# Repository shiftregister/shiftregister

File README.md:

# shiftregister

Software and hardware for the Shift Register project:  http://shiftregister.info/

Muon detection hardware is based on the work of Robert Hart: http://www.hardhack.org.au/projects

Core memory hardware is based on the work of Wayne Holder: https://sites.google.com/site/wayneholder/one-bit-ferrite-core-memory

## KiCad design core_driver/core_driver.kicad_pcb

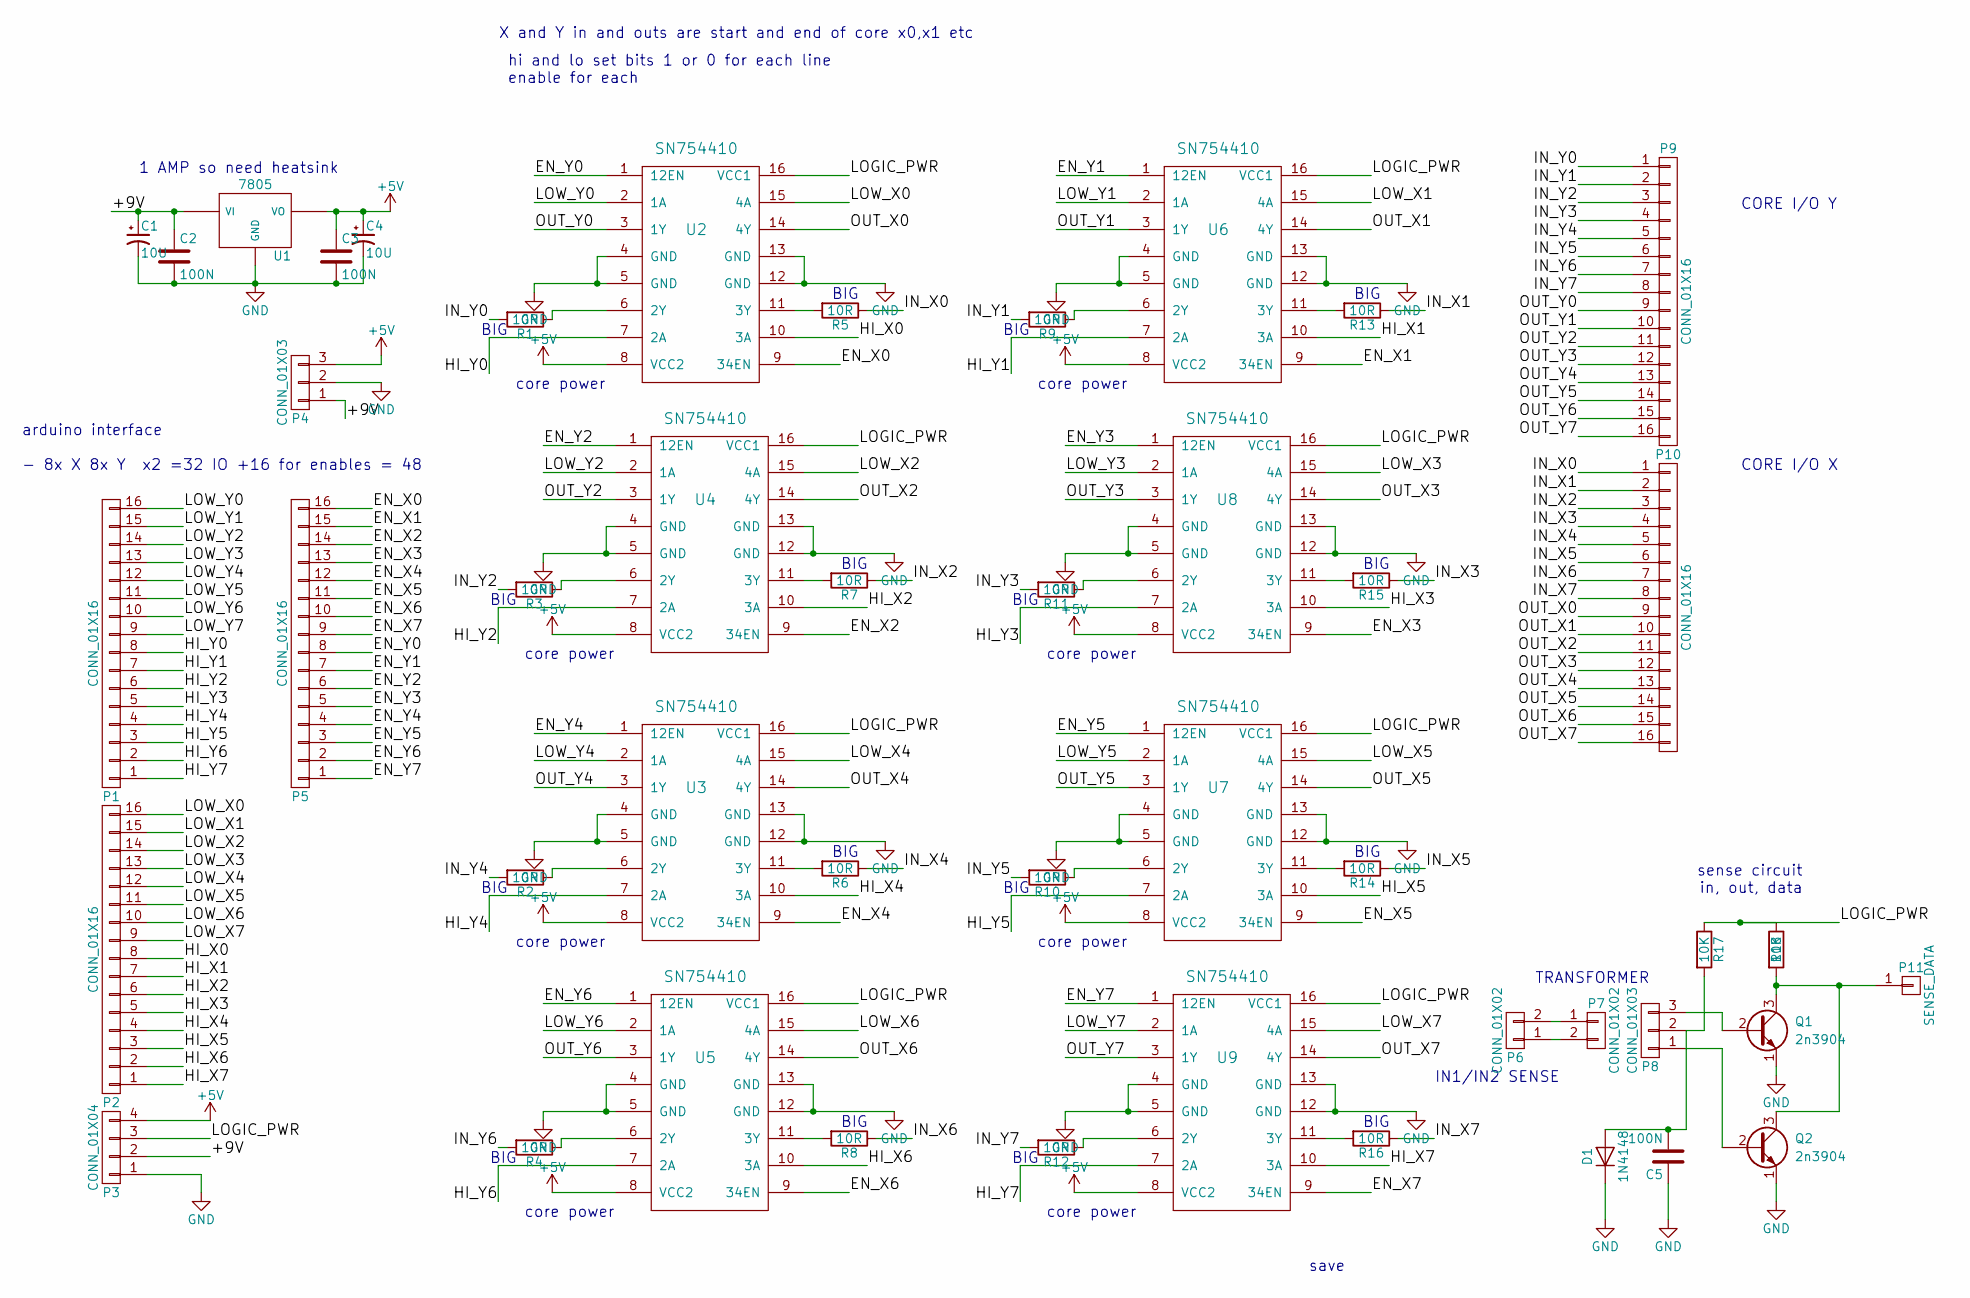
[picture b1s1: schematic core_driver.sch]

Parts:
C1, C4: 10U; CP_Radial_D10.0mm_P5.00mm
C2, C3, C5: 100N; C_Disc_D6.0mm_W2.5mm_P5.00mm
D1: 1N4148; D_DO-35_SOD27_P7.62mm_Horizontal
P1, P2, P5, P9, P10: CONN_01X16; Pin_Header_Straight_1x16_Pitch2.54mm
P3: CONN_01X04; Pin_Header_Straight_1x04_Pitch2.54mm
P4, P8: CONN_01X03; Pin_Header_Straight_1x03_Pitch2.54mm
P6, P7: CONN_01X02; Pin_Header_Straight_1x02_Pitch2.54mm
P11: SENSE_DATA; Pin_Header_Straight_1x01_Pitch2.54mm
Q1, Q2: 2n3904; TO-92_Molded_Wide
R1, R2, R3, R4, R5, R6, R7, R8, R9, R10, R11, R12, R13, R14, R15, R16: 10R; R_Axial_DIN0414_L11.9mm_D4.5mm_P15.24mm_Horizontal
R17, R18: 10K; R_Axial_DIN0204_L3.6mm_D1.6mm_P5.08mm_Horizontal
U1: 7805; TO-220_Vertical
U2, U3, U4, U5, U6, U7, U8, U9: SN754410; DIP-16_W7.62mm_LongPads

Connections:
+5V: C3.1, C4.1, P3.4, P4.3, U1.3, U1.VO, U2.8 (VCC2), U3.8 (VCC2), U4.8 (VCC2), U5.8 (VCC2), U6.8 (VCC2), U7.8 (VCC2), U8.8 (VCC2), U9.8 (VCC2)
/+9V: C1.1, C2.1, P3.2, P4.1, U1.1, U1.VI
/EN_X0: P5.16, U2.9 (34EN)
/EN_X1: P5.15, U6.9 (34EN)
/EN_X2: P5.14, U4.9 (34EN)
/EN_X3: P5.13, U8.9 (34EN)
/EN_X4: P5.12, U3.9 (34EN)
/EN_X5: P5.11, U7.9 (34EN)
/EN_X6: P5.10, U5.9 (34EN)
/EN_X7: P5.9, U9.9 (34EN)
/EN_Y0: P5.8, U2.1 (12EN)
/EN_Y1: P5.7, U6.1 (12EN)
/EN_Y2: P5.6, U4.1 (12EN)
/EN_Y3: P5.5, U8.1 (12EN)
/EN_Y4: P5.4, U3.1 (12EN)
/EN_Y5: P5.3, U7.1 (12EN)
/EN_Y6: P5.2, U5.1 (12EN)
/EN_Y7: P5.1, U9.1 (12EN)
/HI_X0: P2.8, U2.10 (3A)
/HI_X1: P2.7, U6.10 (3A)
/HI_X2: P2.6, U4.10 (3A)
/HI_X3: P2.5, U8.10 (3A)
/HI_X4: P2.4, U3.10 (3A)
/HI_X5: P2.3, U7.10 (3A)
/HI_X6: P2.2, U5.10 (3A)
/HI_X7: P2.1, U9.10 (3A)
/HI_Y0: P1.8, U2.7 (2A)
/HI_Y1: P1.7, U6.7 (2A)
/HI_Y2: P1.6, U4.7 (2A)
/HI_Y3: P1.5, U8.7 (2A)
/HI_Y4: P1.4, U3.7 (2A)
/HI_Y5: P1.3, U7.7 (2A)
/HI_Y6: P1.2, U5.7 (2A)
/HI_Y7: P1.1, U9.7 (2A)
/IN_X0: P10.1, R5.1
/IN_X1: P10.2, R13.1
/IN_X2: P10.3, R7.1
/IN_X3: P10.4, R15.1
/IN_X4: P10.5, R6.1
/IN_X5: P10.6, R14.1
/IN_X6: P10.7, R8.1
/IN_X7: P10.8, R16.1
/IN_Y0: P9.1, R1.2
/IN_Y1: P9.2, R9.2
/IN_Y2: P9.3, R3.2
/IN_Y3: P9.4, R11.2
/IN_Y4: P9.5, R2.2
/IN_Y5: P9.6, R10.2
/IN_Y6: P9.7, R4.2
/IN_Y7: P9.8, R12.2
/LOGIC_PWR: P3.3, R17.1, R18.1, U2.16 (VCC1), U3.16 (VCC1), U4.16 (VCC1), U5.16 (VCC1), U6.16 (VCC1), U7.16 (VCC1), U8.16 (VCC1), U9.16 (VCC1)
/LOW_X0: P2.16, U2.15 (4A)
/LOW_X1: P2.15, U6.15 (4A)
/LOW_X2: P2.14, U4.15 (4A)
/LOW_X3: P2.13, U8.15 (4A)
/LOW_X4: P2.12, U3.15 (4A)
/LOW_X5: P2.11, U7.15 (4A)
/LOW_X6: P2.10, U5.15 (4A)
/LOW_X7: P2.9, U9.15 (4A)
/LOW_Y0: P1.16, U2.2 (1A)
/LOW_Y1: P1.15, U6.2 (1A)
/LOW_Y2: P1.14, U4.2 (1A)
/LOW_Y3: P1.13, U8.2 (1A)
/LOW_Y4: P1.12, U3.2 (1A)
/LOW_Y5: P1.11, U7.2 (1A)
/LOW_Y6: P1.10, U5.2 (1A)
/LOW_Y7: P1.9, U9.2 (1A)
/OUT_X0: P10.9, U2.14 (4Y)
/OUT_X1: P10.10, U6.14 (4Y)
/OUT_X2: P10.11, U4.14 (4Y)
/OUT_X3: P10.12, U8.14 (4Y)
/OUT_X4: P10.13, U3.14 (4Y)
/OUT_X5: P10.14, U7.14 (4Y)
/OUT_X6: P10.15, U5.14 (4Y)
/OUT_X7: P10.16, U9.14 (4Y)
/OUT_Y0: P9.9, U2.3 (1Y)
/OUT_Y1: P9.10, U6.3 (1Y)
/OUT_Y2: P9.11, U4.3 (1Y)
/OUT_Y3: P9.12, U8.3 (1Y)
/OUT_Y4: P9.13, U3.3 (1Y)
/OUT_Y5: P9.14, U7.3 (1Y)
/OUT_Y6: P9.15, U5.3 (1Y)
/OUT_Y7: P9.16, U9.3 (1Y)
GND: C1.2, C2.2, C3.2, C4.2, C5.1, D1.1 (K), P3.1, P4.2, Q1.1 (E), Q2.1 (E), U1.2, U1.GND, U2.4 (GND), U2.5 (GND), U2.12 (GND), U2.13 (GND), U3.4 (GND), U3.5 (GND), U3.12 (GND), U3.13 (GND), U4.4 (GND), U4.5 (GND), U4.12 (GND), U4.13 (GND), U5.4 (GND), U5.5 (GND), U5.12 (GND), U5.13 (GND), U6.4 (GND), U6.5 (GND), U6.12 (GND), U6.13 (GND), U7.4 (GND), U7.5 (GND), U7.12 (GND), U7.13 (GND), U8.4 (GND), U8.5 (GND), U8.12 (GND), U8.13 (GND), U9.4 (GND), U9.5 (GND), U9.12 (GND), U9.13 (GND)
unnamed: C5.2, D1.2 (A), P8.2, R17.2
unnamed: P6.1, P7.2
unnamed: P6.2, P7.1
unnamed: P8.1, Q2.2 (B)
unnamed: P8.3, Q1.2 (B)
unnamed: P11.1, Q1.3 (C), Q2.3 (C), R18.2
unnamed: R1.1, U2.6 (2Y)
unnamed: R2.1, U3.6 (2Y)
unnamed: R3.1, U4.6 (2Y)
unnamed: R4.1, U5.6 (2Y)
unnamed: R5.2, U2.11 (3Y)
unnamed: R6.2, U3.11 (3Y)
unnamed: R7.2, U4.11 (3Y)
unnamed: R8.2, U5.11 (3Y)
unnamed: R9.1, U6.6 (2Y)
unnamed: R10.1, U7.6 (2Y)
unnamed: R11.1, U8.6 (2Y)
unnamed: R12.1, U9.6 (2Y)
unnamed: R13.2, U6.11 (3Y)
unnamed: R14.2, U7.11 (3Y)
unnamed: R15.2, U8.11 (3Y)
unnamed: R16.2, U9.11 (3Y)

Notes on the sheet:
1 AMP so need heatsink
BIG
CORE I/O X
CORE I/O Y
arduino interface - 8x X 8x Y x2 =32 IO +16 for enables = 48
X and Y in and outs are start and end of core x0,x1 etc
hi and lo set bits 1 or 0 for each line enable for each
sense circuit in, out, data
core power
TRANSFORMER
IN1/IN2 SENSE
save

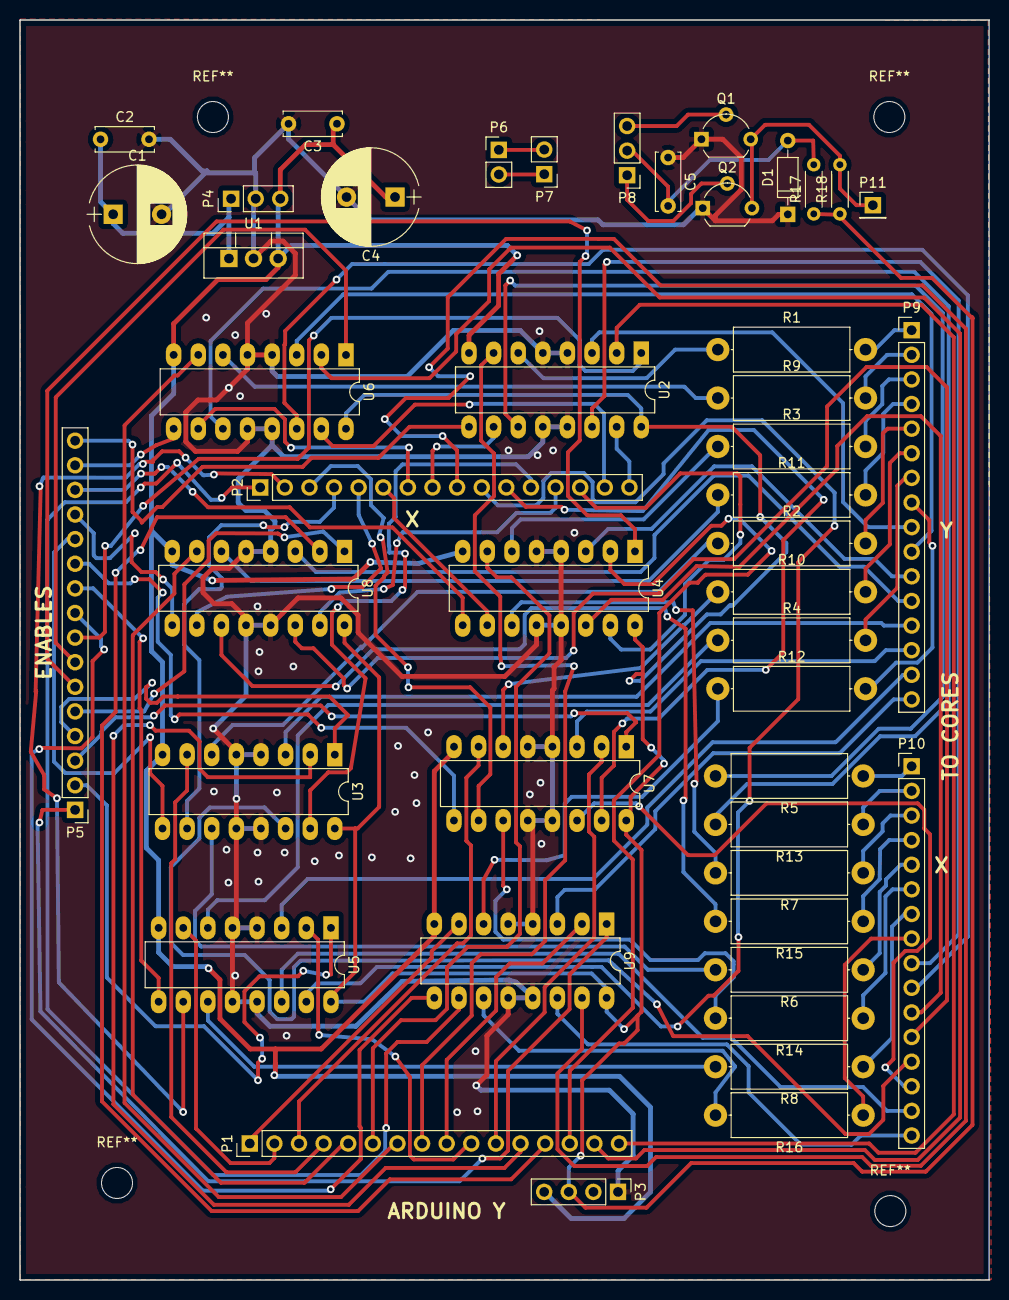
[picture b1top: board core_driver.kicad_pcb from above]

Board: 2 copper layers, 100.0 x 130.0 mm, 46 parts (0 on the bottom side), 106 nets.

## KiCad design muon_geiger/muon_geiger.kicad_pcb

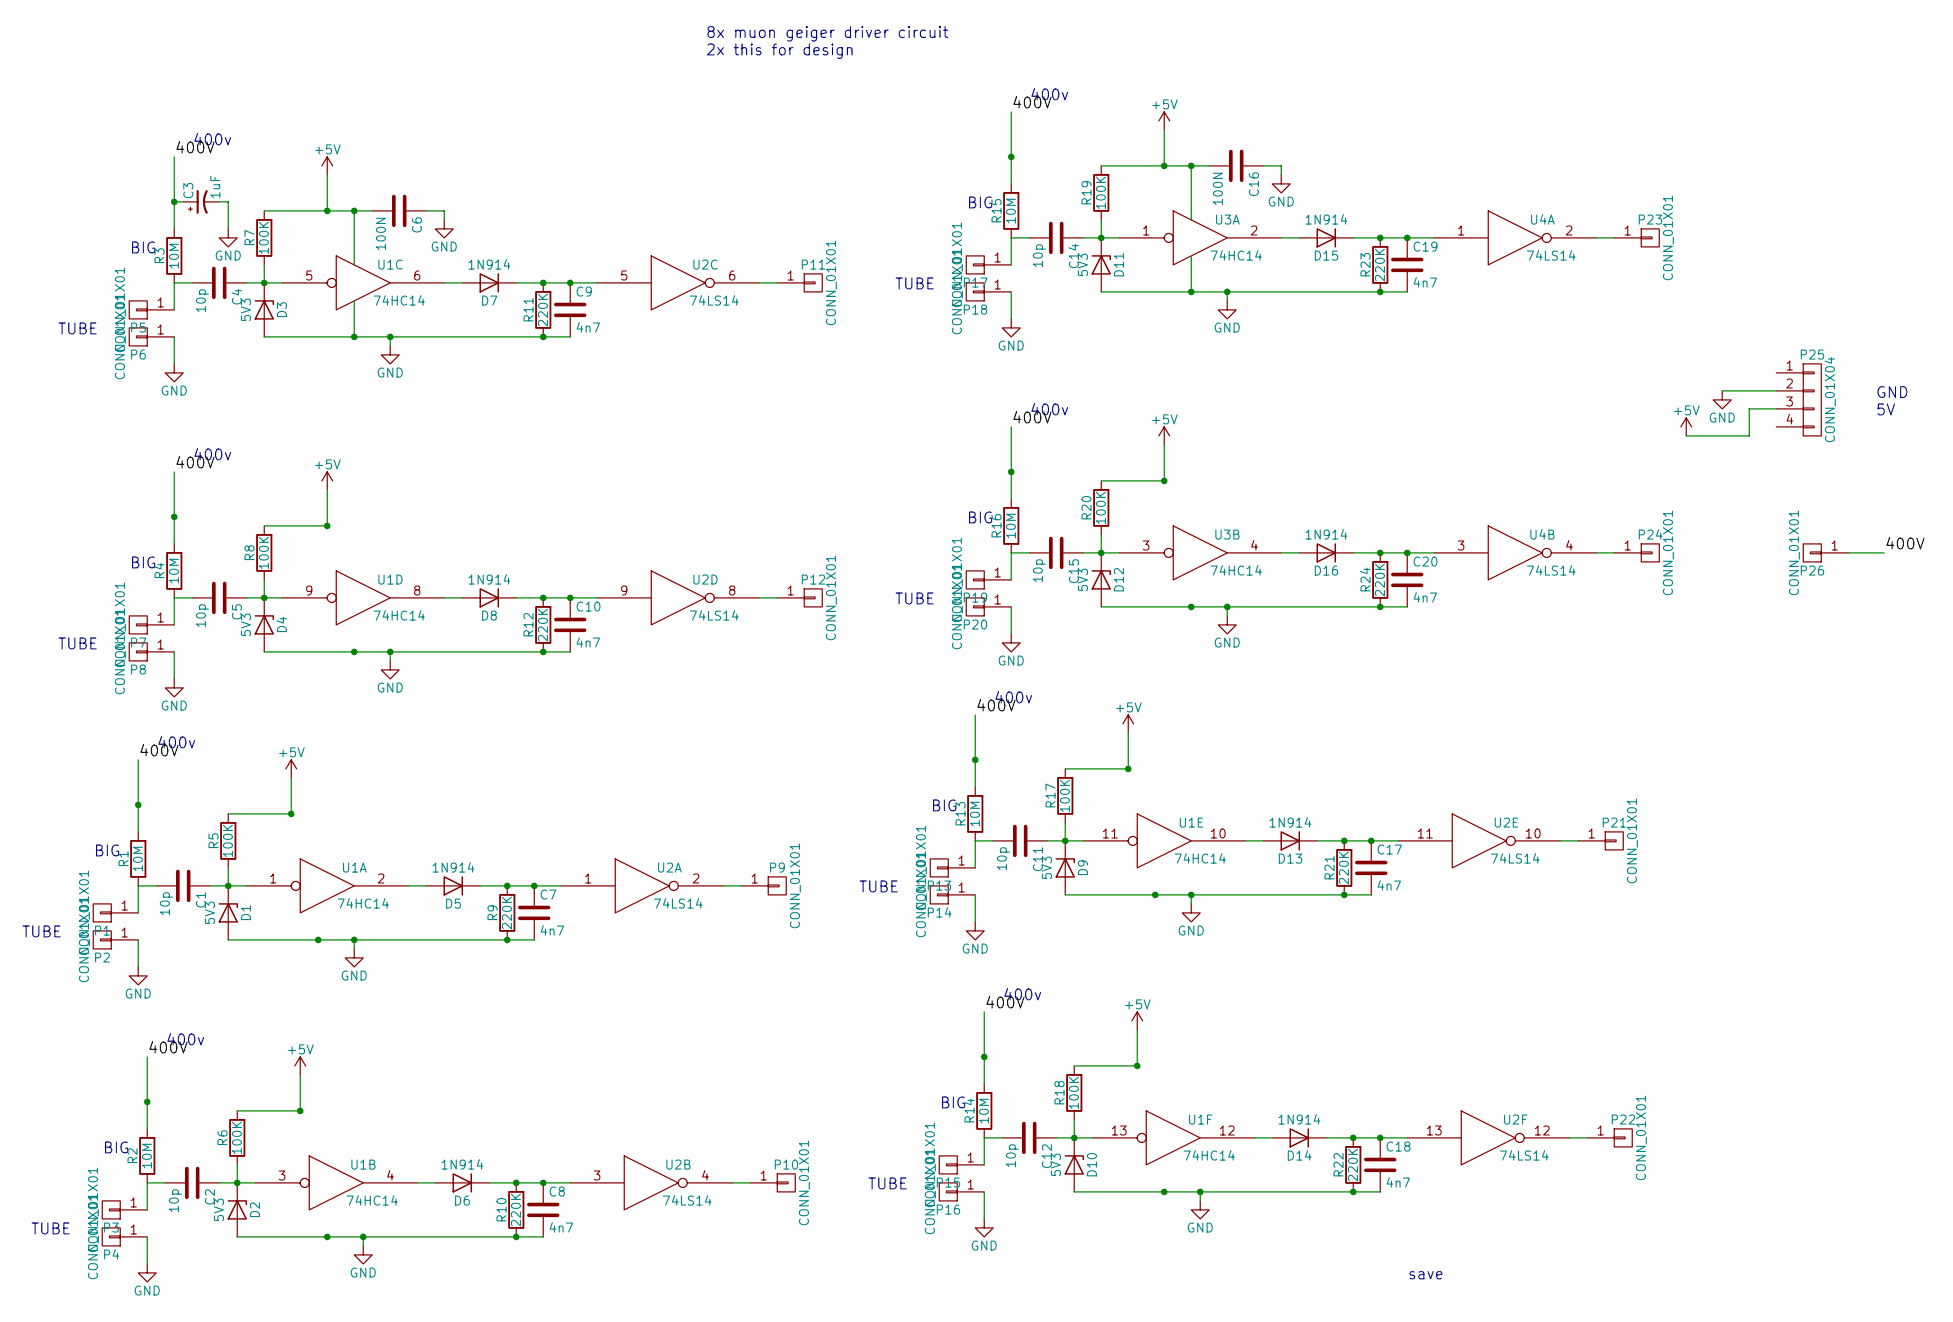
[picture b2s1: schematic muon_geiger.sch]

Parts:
C1, C2, C4, C5, C11, C12, C14, C15: 10p; C_Disc_D6.0mm_W4.4mm_P5.00mm
C3: 1uF; CP_Radial_D10.0mm_P5.00mm
C6, C16: 100N; C_Disc_D3.0mm_W1.6mm_P2.50mm
C7, C8, C9, C10, C17, C18, C19, C20: 4n7; C_Disc_D3.0mm_W1.6mm_P2.50mm
D1, D2, D3, D4, D9, D10, D11, D12: 5V3; D_DO-15_P10.16mm_Horizontal
D5, D6, D7, D8: 1N914; D_DO-35_SOD27_P7.62mm_Horizontal
D13, D14, D15, D16: 1N914; D_DO-15_P10.16mm_Horizontal
P1, P2, P3, P4, P5, P6, P7, P8, P9, P10, P11, P12, P13, P14, P15, P16, P17, P18, P19, P20, P21, P22, P23, P24, P26: CONN_01X01; Pin_Header_Straight_1x01_Pitch2.54mm
P25: CONN_01X04; Pin_Header_Straight_1x04_Pitch2.54mm
R1, R2, R3, R4, R13, R14, R15: 10M; R_Axial_DIN0414_L11.9mm_D4.5mm_P15.24mm_Horizontal
R5, R6, R7, R8, R17, R18, R19, R20: 100K; R_Axial_DIN0207_L6.3mm_D2.5mm_P10.16mm_Horizontal
R9, R10, R11, R12, R21, R22, R23, R24: 220K; R_Axial_DIN0207_L6.3mm_D2.5mm_P10.16mm_Horizontal
R16: 10M; R_Axial_DIN0207_L6.3mm_D2.5mm_P10.16mm_Horizontal
U1, U3: 74HC14; DIP-14_W7.62mm_LongPads
U2, U4: 74LS14; DIP-14_W7.62mm_LongPads

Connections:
+5V: C6.2, C16.2, P25.3, R5.2, R6.2, R7.2, R8.2, R17.2, R18.2, R19.2, R20.2, U1.14 (VCC), U2.14 (VCC), U3.14 (VCC), U4.14 (VCC); also elsewhere on the board
/400V: C3.1, P26.1, R1.2, R2.2, R3.2, R4.2, R13.2, R14.2, R15.2, R16.2
GND: C3.2, C6.1, C7.2, C8.2, C9.2, C10.2, C16.1, C17.2, C18.2, C19.2, C20.2, D1.2 (A), D2.2 (A), D3.2 (A), D4.2 (A), D9.2 (A), D10.2 (A), D11.2 (A), D12.2 (A), P2.1, P4.1, P6.1, P8.1, P14.1, P16.1, P18.1, P20.1, P25.2, R9.1, R10.1, R11.1, R12.1, R21.1, R22.1, R23.1, R24.1, U1.7 (GND), U2.7 (GND), U3.7 (GND), U4.7 (GND); also elsewhere on the board
unnamed: C1.1, D1.1 (K), R5.1, U1.1
unnamed: C1.2, P1.1, R1.1
unnamed: C2.1, D2.1 (K), R6.1, U1.3
unnamed: C2.2, P3.1, R2.1
unnamed: C4.1, D3.1 (K), R7.1, U1.5
unnamed: C4.2, P5.1, R3.1
unnamed: C5.1, D4.1 (K), R8.1, U1.9
unnamed: C5.2, P7.1, R4.1
unnamed: C7.1, D5.1 (K), R9.2, U2.1
unnamed: C8.1, D6.1 (K), R10.2, U2.3
unnamed: C9.1, D7.1 (K), R11.2, U2.5
unnamed: C10.1, D8.1 (K), R12.2, U2.9
unnamed: C11.1, D9.1 (K), R17.1, U1.11
unnamed: C11.2, P13.1, R13.1
unnamed: C12.1, D10.1 (K), R18.1, U1.13
unnamed: C12.2, P15.1, R14.1
unnamed: C14.1, D11.1 (K), R19.1, U3.1
unnamed: C14.2, P17.1, R15.1
unnamed: C15.1, D12.1 (K), R20.1, U3.3
unnamed: C15.2, P19.1, R16.1
unnamed: C17.1, D13.1 (K), R21.2, U2.11
unnamed: C18.1, D14.1 (K), R22.2, U2.13
unnamed: C19.1, D15.1 (K), R23.2, U4.1
unnamed: C20.1, D16.1 (K), R24.2, U4.3
unnamed: D5.2 (A), U1.2
unnamed: D6.2 (A), U1.4
unnamed: D7.2 (A), U1.6
unnamed: D8.2 (A), U1.8
unnamed: D13.2 (A), U1.10
unnamed: D14.2 (A), U1.12
unnamed: D15.2 (A), U3.2
unnamed: D16.2 (A), U3.4
unnamed: P9.1, U2.2
unnamed: P10.1, U2.4
unnamed: P11.1, U2.6
unnamed: P12.1, U2.8
unnamed: P21.1, U2.10
unnamed: P22.1, U2.12
unnamed: P23.1, U4.2
unnamed: P24.1, U4.4

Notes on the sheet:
8x muon geiger driver circuit 2x this for design
400v
TUBE
BIG
GND 5V
save

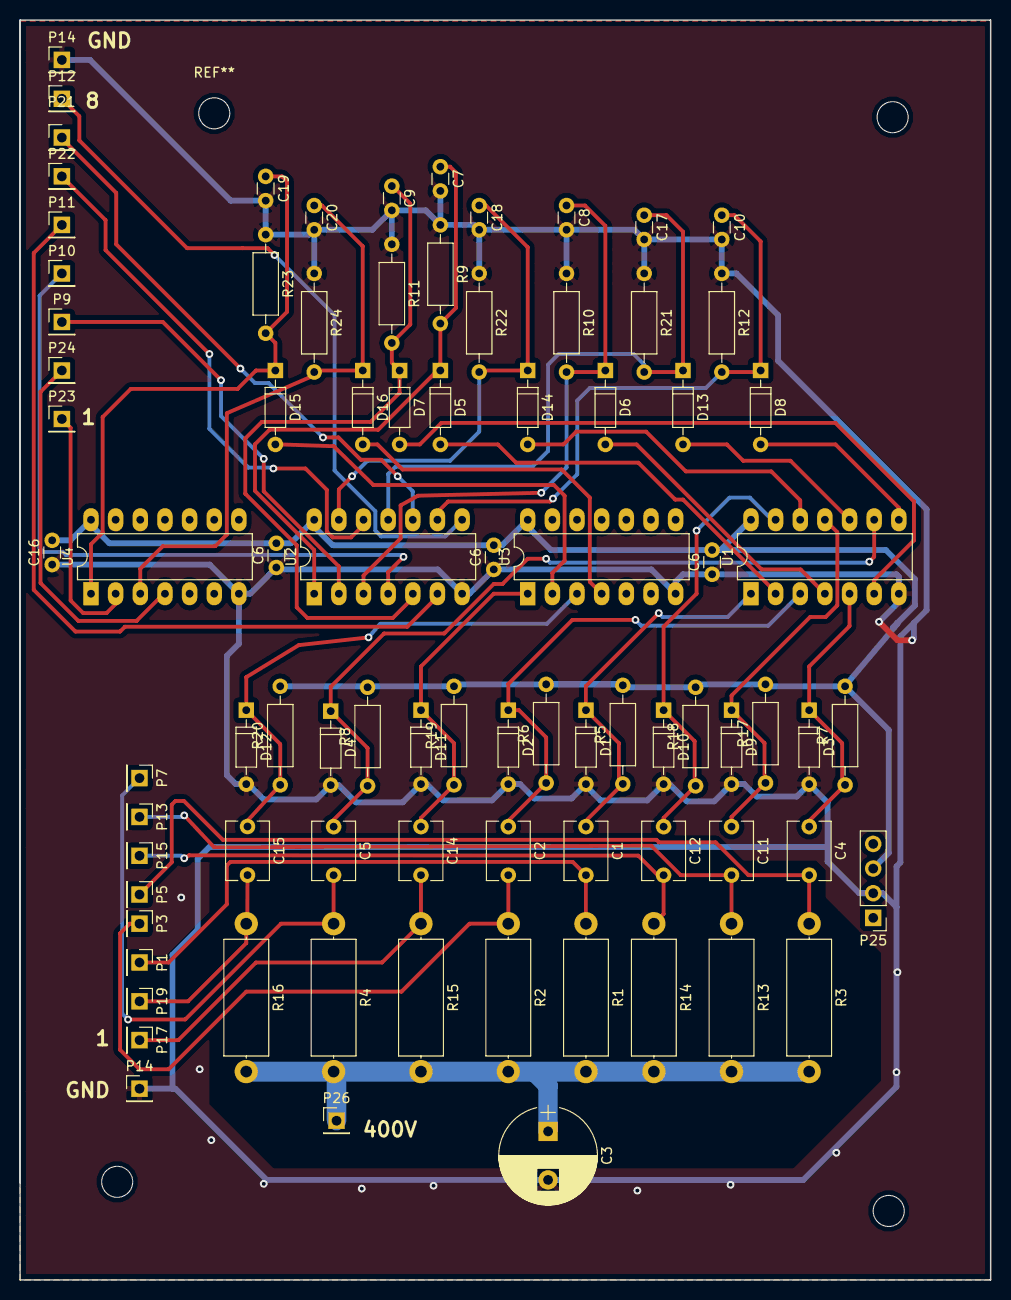
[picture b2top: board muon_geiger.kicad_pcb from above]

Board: 2 copper layers, 100.0 x 129.8 mm, 85 parts (0 on the bottom side), 43 nets.

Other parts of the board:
C6#2, C6#3: 100N; C_Disc_D3.0mm_W1.6mm_P2.50mm
P14#2: CONN_01X01; Pin_Header_Straight_1x01_Pitch2.54mm

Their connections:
+5V: C6#2.2, C6#3.2; also elsewhere on the board
GND: C6#2.1, C6#3.1, P14#2.1; also elsewhere on the board

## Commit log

2017-07-25 first commit for software and hardware
2017-07-25 added
2017-07-26 finalising
2017-08-17 final
2017-09-12 core and muon drivers
2018-05-09 added for logging gps/etrex and sds particle sensor
2018-05-21 howtos
2018-07-05 added early messene softwares
